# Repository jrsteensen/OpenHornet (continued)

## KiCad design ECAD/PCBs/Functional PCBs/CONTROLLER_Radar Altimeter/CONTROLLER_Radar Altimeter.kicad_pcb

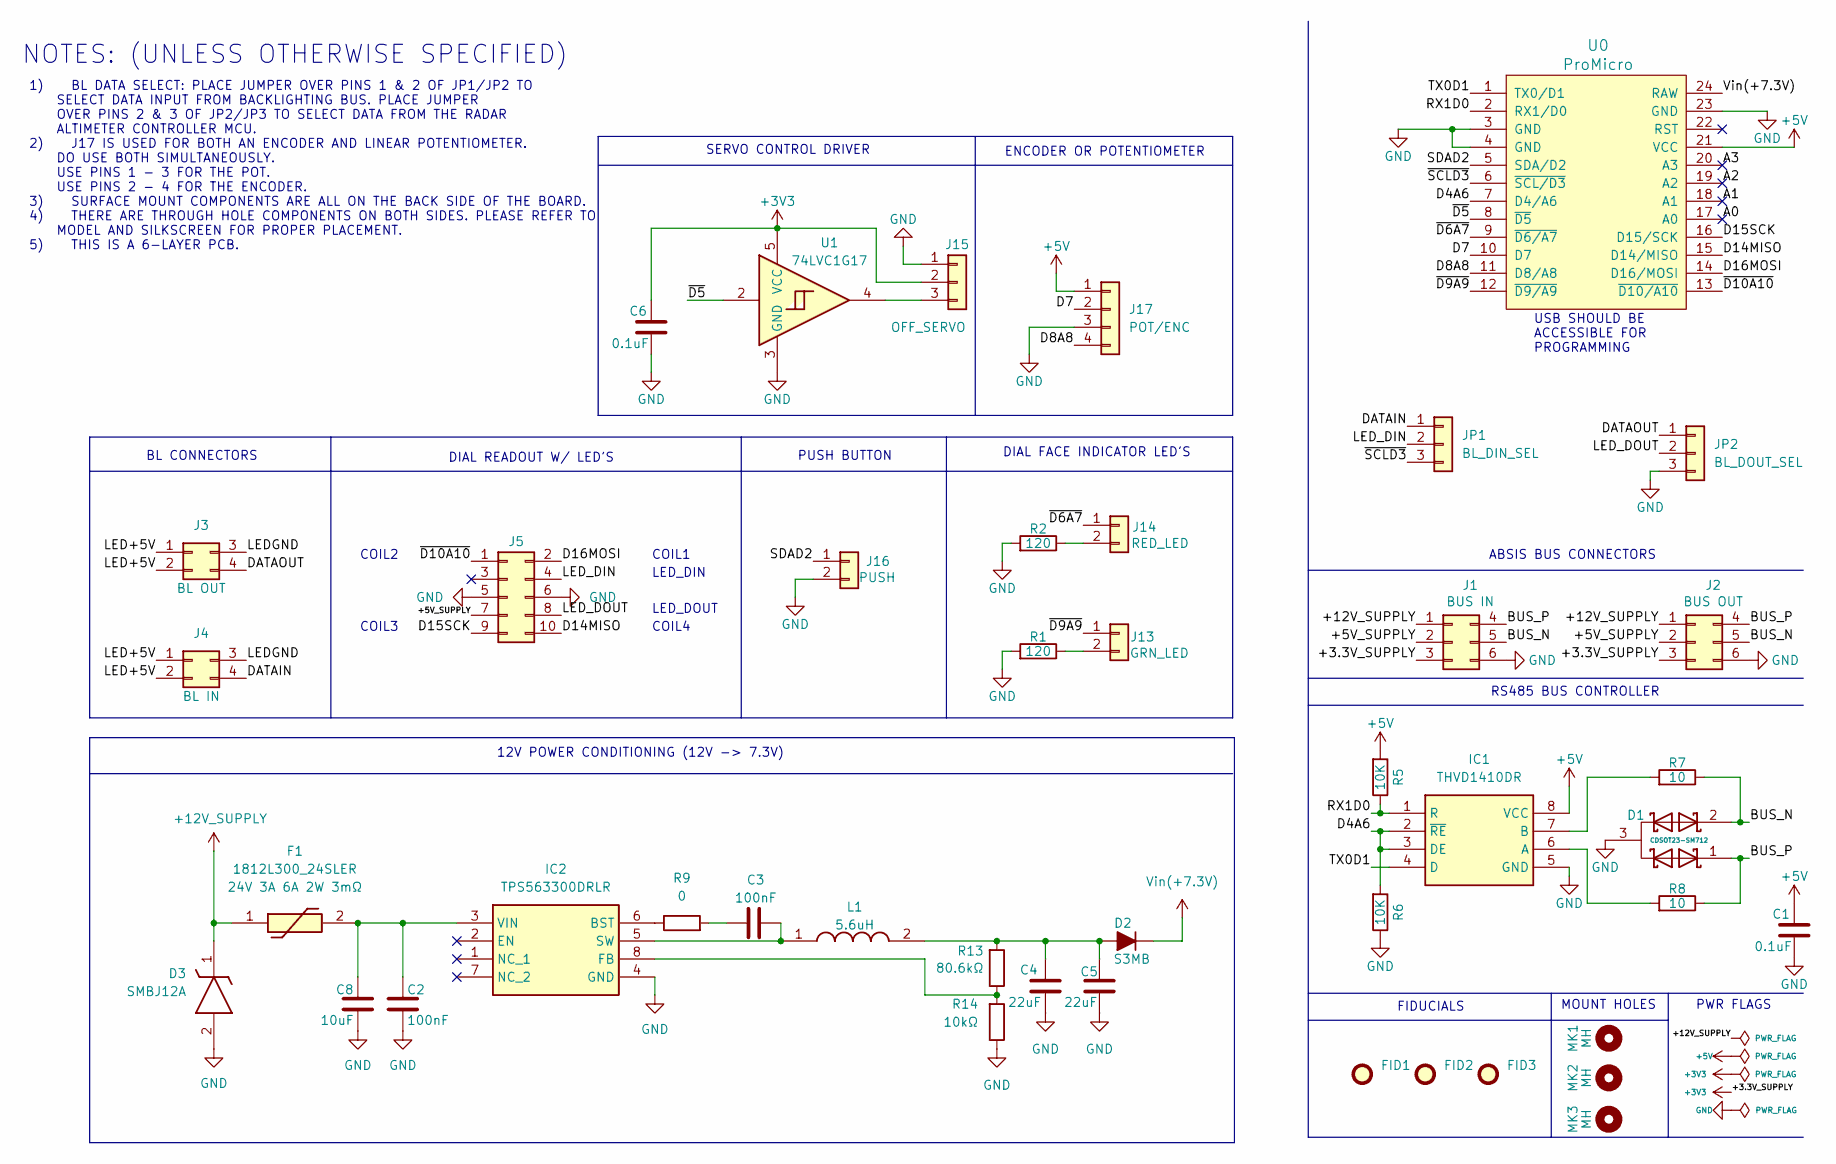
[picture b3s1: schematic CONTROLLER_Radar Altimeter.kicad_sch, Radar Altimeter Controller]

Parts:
C1, C6: 0.1uF; C_0603_1608Metric; Manufacturer PN CC0603KRX7R9BB104; LCSC C14663
C2, C3: 100nF; C_0402_1005Metric; Manufacturer PN CL05B104KB54PNC; LCSC C307331
C4, C5: 22uF; C_0805_2012Metric; Manufacturer PN CL21A226MAQNNNE; LCSC C45783
C8: 10uF; C_0603_1608Metric; Manufacturer PN CL10A106MA8NRNC; LCSC C96446
D1: CDSOT23-SM712; Manufacturer_Part_Number CDSOT23-SM712; Mouser Part Number 652-CDSOT23-SM712
D2: S3MB; D_SMB; Manufacturer PN S3MB; LCSC C47524
D3: SMBJ12A; D_SMB; Manufacturer PN SMBJ12A; LCSC C151251
F1: 1812L300_24SLER; Fuse_1812_4532Metric; Manufacturer PN 1812L300/24SLER; LCSC C1512049
FID1, FID2, FID3: Fiducial; Fiducial_1mm_Mask2mm
IC1: THVD1410DR; Manufacturer_Part_Number THVD1410DR; Mouser Part Number 595-THVD1410DR
IC2: TPS563300DRLR; SOT-583-8; Manufacturer PN TPS563300DRLR; LCSC C5219249
J1: BUS IN; Molex_Mini-Fit_Jr_5566-06A_2x03_P4.20mm_Vertical; Manufacturer PN 39-28-1063; LCSC C471417
J2: BUS OUT; Molex_Mini-Fit_Jr_5566-06A_2x03_P4.20mm_Vertical; Manufacturer PN 39-28-1063; LCSC C471417
J3: BL OUT; Molex_Mini-Fit_Jr_5566-04A_2x02_P4.20mm_Vertical; Manufacturer PN 39-28-1043; LCSC C293502
J4: BL IN; Molex_Mini-Fit_Jr_5566-04A_2x02_P4.20mm_Vertical; Manufacturer PN 39-28-1043; LCSC C293502
J5: Conn_02x05_Odd_Even; PinHeader_2x05_P2.54mm_Vertical
J13: GRN_LED; PinHeader_1x02_P2.54mm_Vertical; Manufacturer PN PH1-02-UA
J14: RED_LED; PinHeader_1x02_P2.54mm_Vertical; Manufacturer PN PH1-02-UA
J15: OFF_SERVO; Adam-Tech_1x03_P1.25mm_Vertical; Manufacturer PN PH1-03-UA
J16: PUSH; PinHeader_1x02_P2.54mm_Vertical; Manufacturer PN PH1-02-UA
J17: POT/ENC; PinHeader_1x04_P2.54mm_Vertical
JP1: BL_DIN_SEL; PinHeader_1x03_P2.54mm_Vertical
JP2: BL_DOUT_SEL; PinHeader_1x03_P2.54mm_Vertical
L1: 5.6uH; L_Bourns_SRP6060FA; Manufacturer PN SRP6060FA-5R6M; LCSC C1332221
MK1, MK2, MK3: MH; MountingHole_2.5mm
R1, R2: 120; R_0805_2012Metric_Pad1.15x1.40mm_HandSolder; Manufacturer PN 0805W8F1200T5E; LCSC C17437
R5, R6: 10K; R_0603_1608Metric_Pad0.98x0.95mm_HandSolder; LCSC C25804
R7, R8: 10; R_0603_1608Metric_Pad0.98x0.95mm_HandSolder; LCSC C844519
R9: 0; R_0402_1005Metric; Manufacture PN 0402WGF0000TCE; LCSC C17168
R13: 80.6kΩ; R_0402_1005Metric; Manufacturer PN 0402WGF8062TCE; LCSC C25921
R14: 10kΩ; R_0402_1005Metric; Manufacturer PN 0402WGF1002TCE; LCSC C25744
U0: ProMicro; DIP-24_W15.24mm_Socket; LCSC C72120
U1: 74LVC1G17; SOT-23-5; LCSC C7836

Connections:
+3V3: C6.2, J1.3, J2.3, J15.2, U1.5 (VCC)
+5V: C1.2, IC1.8 (VCC), J17.1, R5.2, U0.21 (VCC)
+12V_SUPPLY: D3.1 (K), F1.1, J1.1, J2.1
/+5V_SUPPLY: J1.2, J2.2, J5.7
/A0: U0.17 (A0)
/A1: U0.18 (A1)
/A2: U0.19 (A2)
/A3: U0.20 (A3)
/BUS_N: D1.2, J1.5, J2.5, R7.2
/BUS_P: D1.1, J1.4, J2.4, R8.2
/D4A6: IC1.2 (~RE), IC1.3 (DE), R6.2, U0.7 (D4/A6)
/D7: J17.2, U0.10 (D7)
/D8A8: J17.4, U0.11 (D8/A8)
/D14MISO: J5.10, U0.15 (D14/MISO)
/D15SCK: J5.9, U0.16 (D15/SCK)
/D16MOSI: J5.2, U0.14 (D16/MOSI)
/DATAIN: J4.4, JP1.1
/DATAOUT: J3.4, JP2.1
/LED+5V: J3.1, J3.2 (Pin_3), J4.1, J4.2 (Pin_3)
/LEDGND: J3.3 (Pin_2), J4.3 (Pin_2)
/LED_DIN: J5.4, JP1.2
/LED_DOUT: J5.8, JP2.2
/RX1D0: IC1.1 (R), R5.1, U0.2 (RX1/D0)
/SDAD2: J16.1, U0.5 (SDA/D2)
/TX0D1: IC1.4 (D), U0.1 (TX0/D1)
/~D5: U0.8 (~D5), U1.2
/~D6A7: J14.1, U0.9 (~D6/A7)
/~D9A9: J13.1, U0.12 (~D9/A9)
/~D10A10: J5.1, U0.13 (~D10/A10)
/~SCLD3: JP1.3, U0.6 (~SCL/D3)
GND: C1.1, C2.1, C4.2, C5.2, C6.1, C8.1, D1.3, D3.2 (A), IC1.5 (GND), IC2.4 (GND), J1.6, J2.6, J5.5, J5.6, J15.1, J16.2, J17.3, JP2.3, R1.1, R2.1, R6.1, R14.1, U0.3 (GND), U0.4 (GND), U0.23 (GND), U1.3 (GND)
unnamed: C3.2, R9.2
unnamed: C4.1, C5.1, D2.2 (A), L1.2, R13.2
unnamed: IC1.6 (A), R8.1
unnamed: IC1.7 (B), R7.1
unnamed: IC2.6 (BST), R9.1
unnamed: IC2.8 (FB), R13.1, R14.2
unnamed: C3.1, IC2.5 (SW), L1.1
unnamed: C2.2, C8.2, F1.2, IC2.3 (VIN)
unnamed: J13.2, R1.2
unnamed: J14.2, R2.2
unnamed: J15.3, U1.4
Vin(+7.3V): D2.1 (K), U0.24 (RAW)

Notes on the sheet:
ABSIS BUS CONNECTORS
RS485 BUS CONTROLLER
12V POWER CONDITIONING (12V -> 7.3V)
USB SHOULD BE ACCESSIBLE FOR PROGRAMMING
MOUNT HOLES
COIL3
FIDUCIALS
DIAL READOUT W/ LED'S
COIL4
ENCODER OR POTENTIOMETER
NOTES: (UNLESS OTHERWISE SPECIFIED)
PUSH BUTTON
LED_DOUT
1) BL DATA SELECT: PLACE JUMPER OVER PINS 1 & 2 OF JP1/JP2 TO SELECT DATA INPUT FROM BACKLIGHTING BUS. PLACE JUMPER OVER PINS 2 & 3 OF JP2/JP3 TO SELECT DATA FROM THE RADAR ALTIMETER CONTROLLER MCU. 2) J17 IS USED FOR BOTH AN ENCODER AND LINEAR POTENTIOMETER. DO USE BOTH SIMULTANEOUSLY. USE PINS 1 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
COIL2
COIL1
DIAL FACE INDICATOR LED'S
PWR FLAGS
LED_DIN
SERVO CONTROL DRIVER
BL CONNECTORS

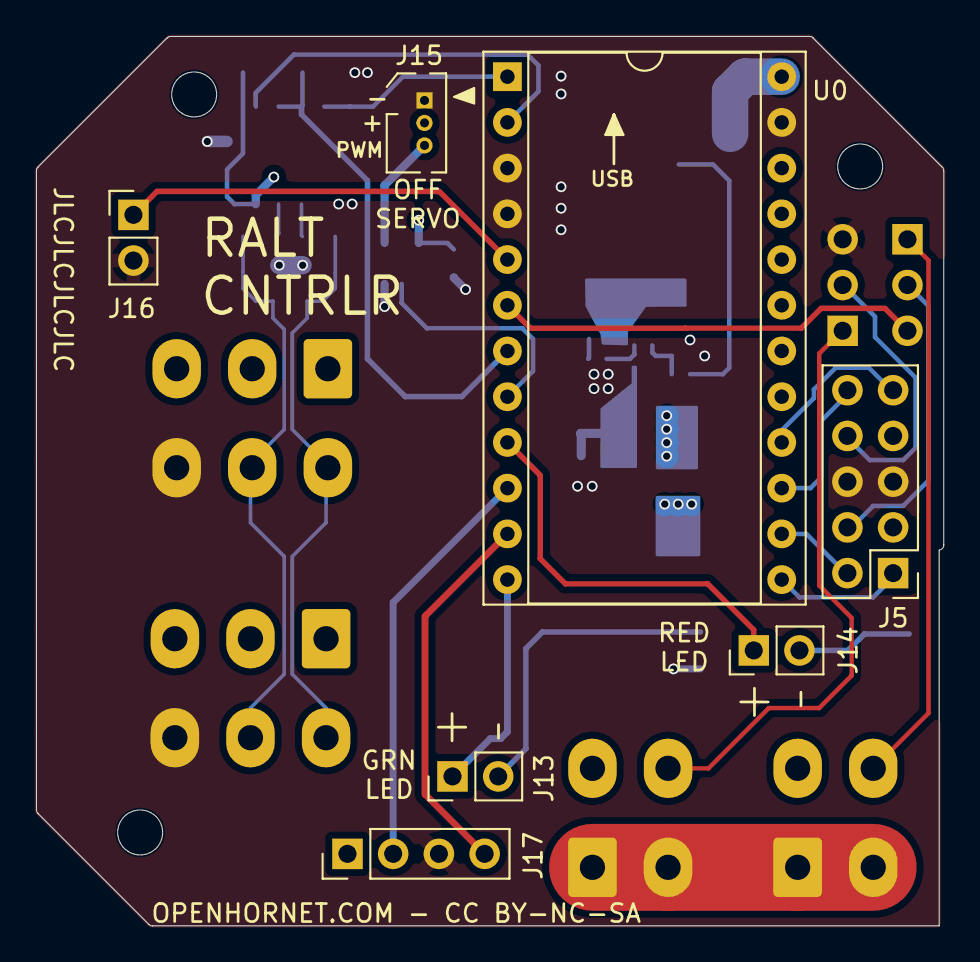
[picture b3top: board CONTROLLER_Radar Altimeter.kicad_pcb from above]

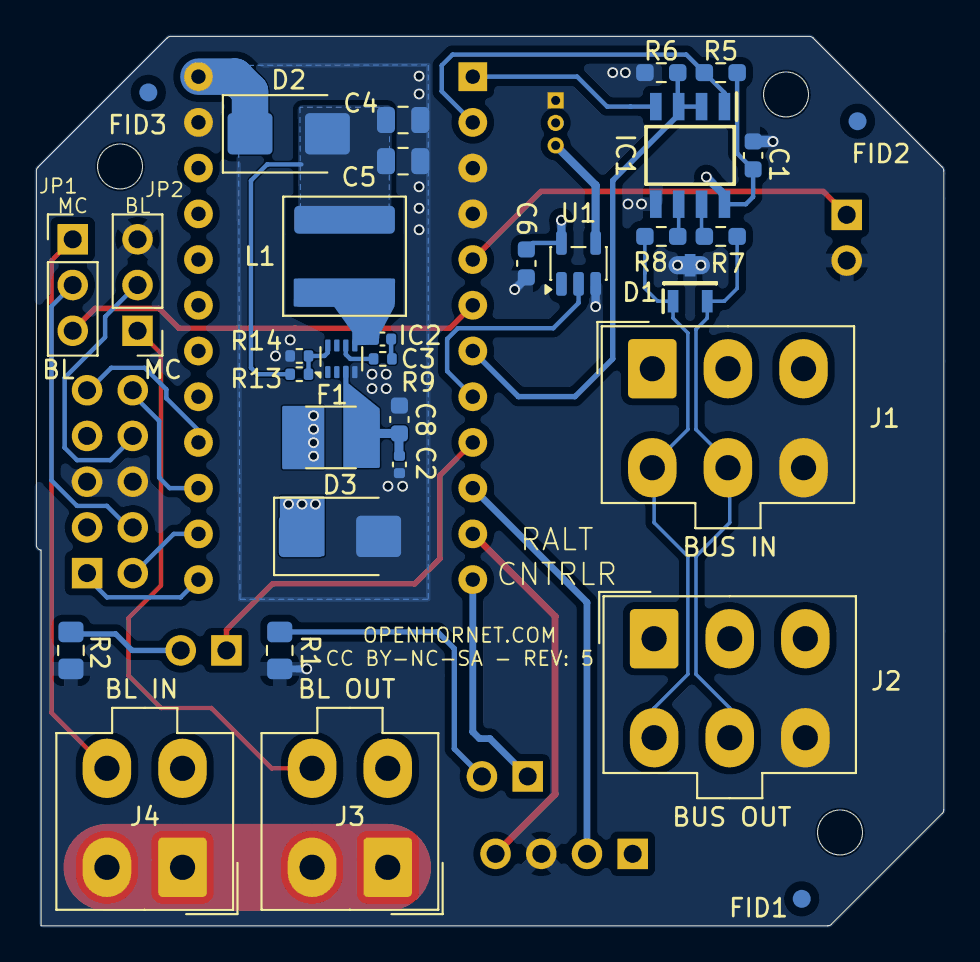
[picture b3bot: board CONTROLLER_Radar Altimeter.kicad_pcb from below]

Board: 6 copper layers, 50.4 x 49.4 mm, 43 parts (33 on the bottom side), 39 nets.

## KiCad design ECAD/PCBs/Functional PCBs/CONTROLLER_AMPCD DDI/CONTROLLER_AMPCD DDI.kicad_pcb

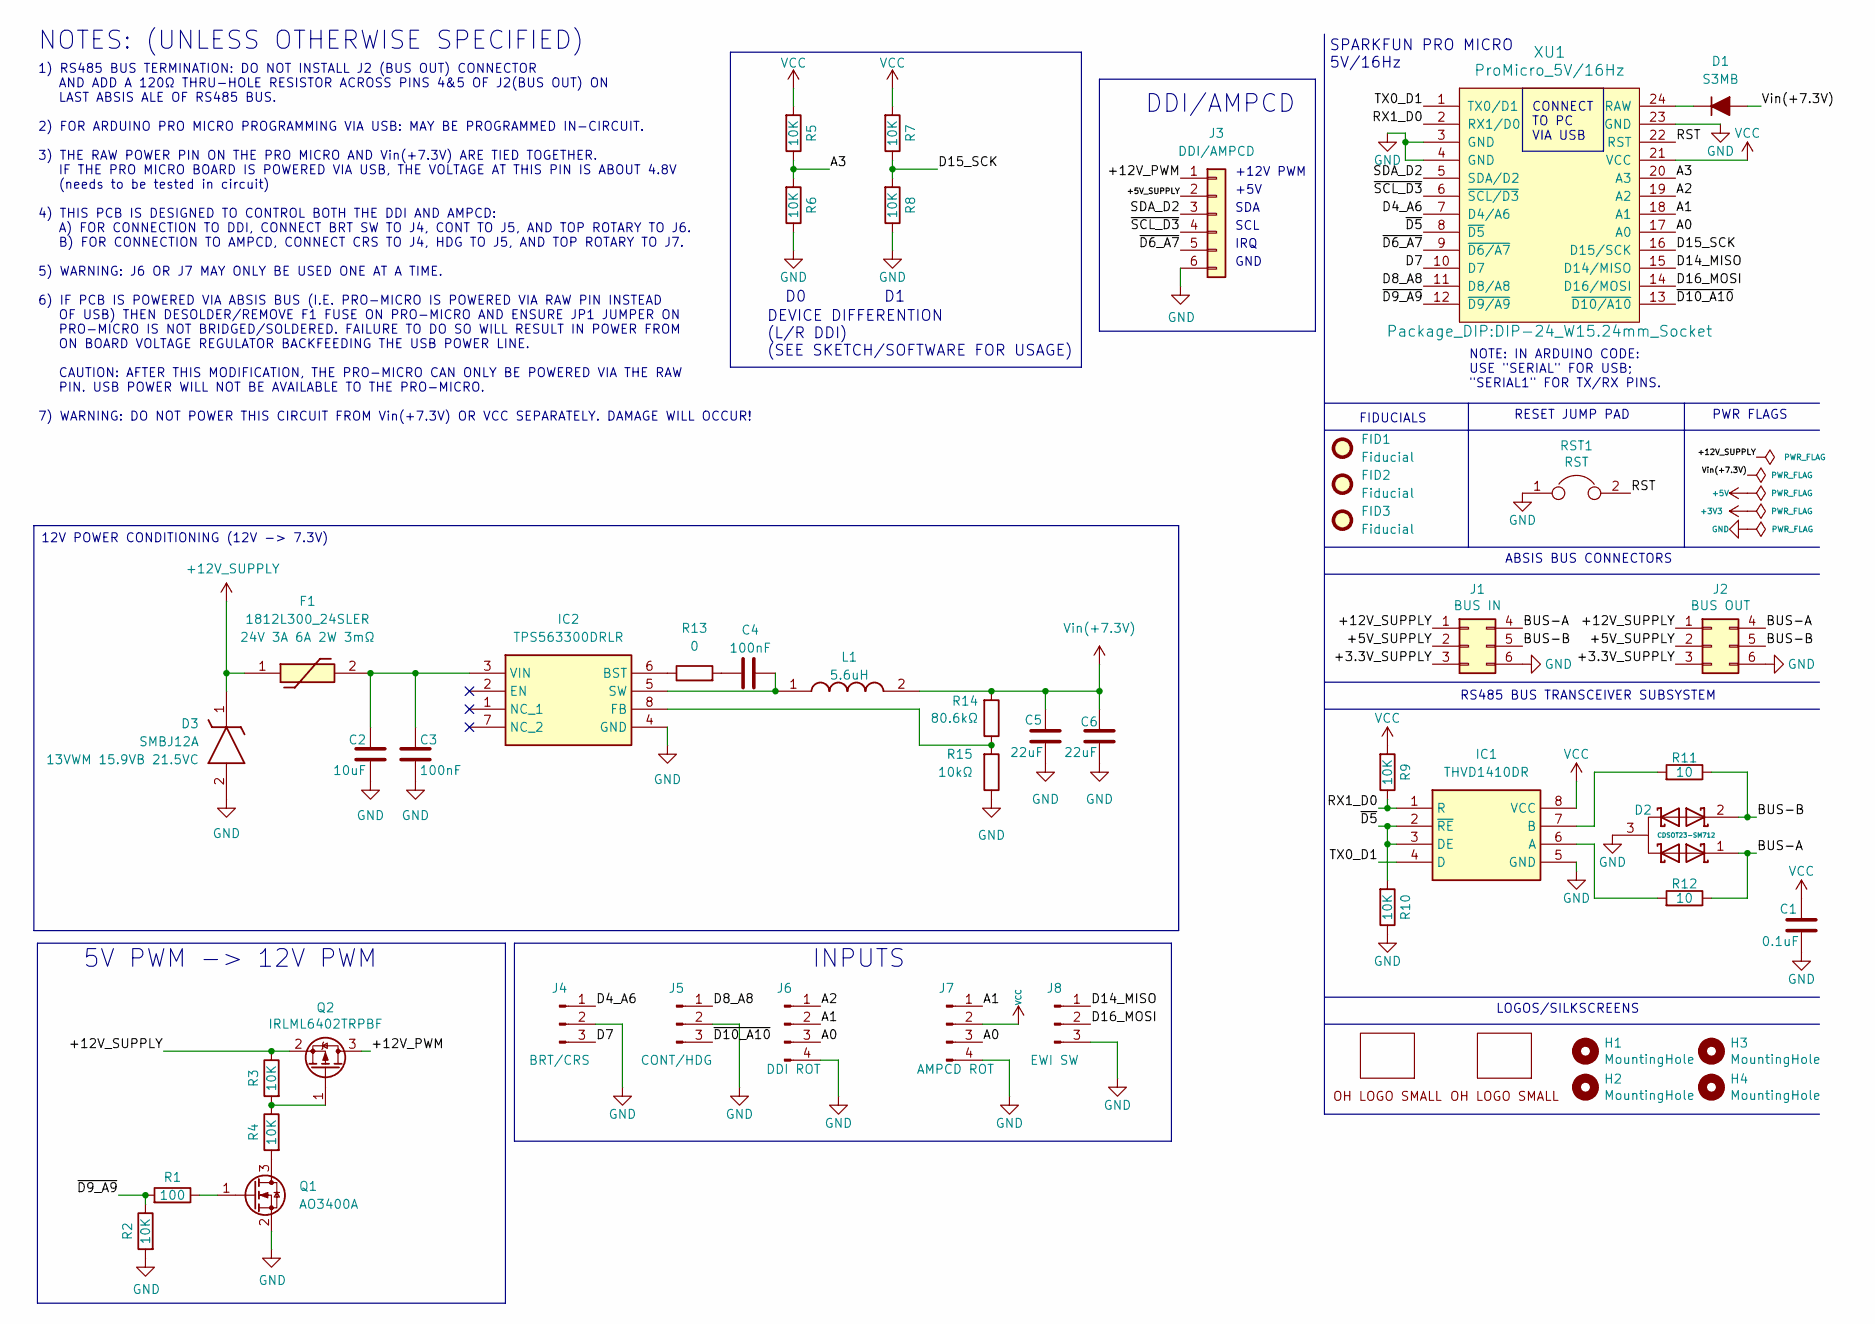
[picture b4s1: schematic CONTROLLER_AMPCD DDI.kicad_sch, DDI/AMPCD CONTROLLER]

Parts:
C1: 0.1uF; C_0603_1608Metric; Manufacturer PN CC0603KRX7R9BB104; LCSC C14663
C2: 10uF; C_0603_1608Metric; Manufacturer PN CL10A106MA8NRNC; LCSC C96446
C3, C4: 100nF; C_0402_1005Metric; Manufacturer PN CL05B104KB54PNC; LCSC C307331
C5, C6: 22uF; C_0805_2012Metric; Manufacturer PN CL21A226MAQNNNE; LCSC C45783
D1: S3MB; D_SMB; Manufacturer PN S3MB; LCSC C47524
D2: CDSOT23-SM712; Manufacturer_Part_Number CDSOT23-SM712; Mouser Part Number 652-CDSOT23-SM712
D3: SMBJ12A; D_SMB; Manufacturer PN SMBJ12A; LCSC C151251
F1: 1812L300_24SLER; Fuse_1812_4532Metric; Manufacturer PN 1812L300/24SLER; LCSC C1512049
FID1, FID2, FID3: Fiducial; Fiducial_1mm_Mask2mm
H1, H2, H3, H4: MountingHole; MountingHole_3.2mm_M3
IC1: THVD1410DR; Manufacturer_Part_Number THVD1410DR; Mouser Part Number 595-THVD1410DR
IC2: TPS563300DRLR; SOT-583-8; Manufacturer PN TPS563300DRLR; LCSC C5219249
J1: BUS IN; Molex_Mini-Fit_Jr_5566-06A2_2x03_P4.20mm_Vertical; LCSC N/A
J2: BUS OUT; Molex_Mini-Fit_Jr_5566-06A2_2x03_P4.20mm_Vertical; LCSC N/A
J3: DDI/AMPCD; Molex_KK-254_AE-6410-06A_1x06_P2.54mm_Vertical
J4: BRT/CRS; Molex_KK-254_AE-6410-03A_1x03_P2.54mm_Vertical
J5: CONT/HDG; Molex_KK-254_AE-6410-03A_1x03_P2.54mm_Vertical
J6: DDI ROT; Molex_KK-254_AE-6410-04A_1x04_P2.54mm_Vertical
J7: AMPCD ROT; Molex_KK-254_AE-6410-04A_1x04_P2.54mm_Vertical
J8: EWI SW; Molex_KK-254_AE-6410-03A_1x03_P2.54mm_Vertical
L1: 5.6uH; L_Bourns_SRP6060FA; Manufacturer PN SRP6060FA-5R6M; LCSC C1332221
LOGO1: OpenHornetLogoSmall; LOGO_OH_NoText_Small; LCSC N/A
LOGO2: OpenHornetLogoSmall; LOGO_OH_Text_Small; LCSC N/A
Q1: AO3400A; SOT-23; Manufacture PN AO3400A; LCSC C20917
Q2: IRLML6402TRPBF; SOT-23; LCSC C2593
R1: 100; R_0603_1608Metric_Pad0.98x0.95mm_HandSolder; LCSC C22775
R2, R3, R4, R5, R6, R7, R8, R9, R10: 10K; R_0603_1608Metric_Pad0.98x0.95mm_HandSolder; LCSC C25804
R11, R12: 10; R_0603_1608Metric_Pad0.98x0.95mm_HandSolder; LCSC C844519
R13: 0; R_0402_1005Metric; Manufacture PN 0402WGF0000TCE; LCSC C17168
R14: 80.6kΩ; R_0402_1005Metric; Manufacturer PN 0402WGF8062TCE; LCSC C25921
R15: 10kΩ; R_0402_1005Metric; Manufacturer PN 0402WGF1002TCE; LCSC C25744
RST1: RST; SolderJumper-2_P1.3mm_Open_RoundedPad1.0x1.5mm
XU1: ProMicro_5V/16Hz; DIP-24_W15.24mm_Socket; LCSC C72120

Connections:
+12V_SUPPLY: D3.1 (K), F1.1, J1.1, J2.1, Q2.2 (S), R3.1
/+3.3V_SUPPLY: J1.3, J2.3
/+5V_SUPPLY: J1.2, J2.2, J3.2
/+12V_PWM: J3.1, Q2.3 (D)
/A0: J6.3, J7.3, XU1.17 (A0)
/A1: J6.2, J7.1, XU1.18 (A1)
/A2: J6.1, XU1.19 (A2)
/A3: R5.1, R6.2, XU1.20 (A3)
/BUS-A: D2.1, J1.4, J2.4, R12.2
/BUS-B: D2.2, J1.5, J2.5, R11.2
/D4_A6: J4.1, XU1.7 (D4/A6)
/D7: J4.3, XU1.10 (D7)
/D8_A8: J5.1, XU1.11 (D8/A8)
/D14_MISO: J8.1, XU1.15 (D14/MISO)
/D15_SCK: R7.1, R8.2, XU1.16 (D15/SCK)
/D16_MOSI: J8.2, XU1.14 (D16/MOSI)
/RST: RST1.2, XU1.22 (RST)
/RX1_D0: IC1.1 (R), R9.1, XU1.2 (RX1/D0)
/SDA_D2: J3.3, XU1.5 (SDA/D2)
/TX0_D1: IC1.4 (D), XU1.1 (TX0/D1)
/~D5: IC1.2 (~RE), IC1.3 (DE), R10.2, XU1.8 (~D5)
/~D6_A7: J3.5, XU1.9 (~D6/A7)
/~D9_A9: R1.2, R2.1, XU1.12 (~D9/A9)
/~D10_A10: J5.3, XU1.13 (~D10/A10)
/~SCL_D3: J3.4, XU1.6 (~SCL/D3)
GND: C1.1, C2.1, C3.1, C5.2, C6.2, D2.3, D3.2 (A), IC1.5 (GND), IC2.4 (GND), J1.6, J2.6, J3.6, J4.2, J5.2, J6.4, J7.4, J8.3, Q1.2 (S), R2.2, R6.1, R8.1, R10.1, R15.1, RST1.1, XU1.3 (GND), XU1.4 (GND), XU1.23 (GND)
unnamed: C4.2, R13.2
unnamed: D1.1 (K), XU1.24 (RAW)
unnamed: IC1.6 (A), R12.1
unnamed: IC1.7 (B), R11.1
unnamed: IC2.6 (BST), R13.1
unnamed: IC2.8 (FB), R14.1, R15.2
unnamed: C4.1, IC2.5 (SW), L1.1
unnamed: C2.2, C3.2, F1.2, IC2.3 (VIN)
unnamed: Q1.3 (D), R4.2
unnamed: Q1.1 (G), R1.1
unnamed: Q2.1 (G), R3.2, R4.1
VCC: C1.2, IC1.8 (VCC), J7.2, R5.2, R7.2, R9.2, XU1.21 (VCC)
Vin(+7.3V): C5.1, C6.1, D1.2 (A), L1.2, R14.2

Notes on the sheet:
IRQ
FIDUCIALS
RS485 BUS TRANSCEIVER SUBSYSTEM
NOTES: (UNLESS OTHERWISE SPECIFIED)
DEVICE DIFFERENTION (L/R DDI) (SEE SKETCH/SOFTWARE FOR USAGE)
SPARKFUN PRO MICRO 5V/16Hz
CONNECT TO PC VIA USB
RESET JUMP PAD
LOGOS/SILKSCREENS
+12V PWM
5V PWM -> 12V PWM
SCL
PWR FLAGS
+5V
ABSIS BUS CONNECTORS
NOTE: IN ARDUINO CODE: USE "SERIAL" FOR USB; "SERIAL1" FOR TX/RX PINS.
SDA
INPUTS
1) RS485 BUS TERMINATION: DO NOT INSTALL J2 (BUS OUT) CONNECTOR AND ADD A 120Ω THRU-HOLE RESISTOR ACROSS PINS 4&5 OF J2(BUS OUT) ON LAST ABSIS ALE OF RS485 BUS. 2) FOR ARDUINO PRO MICRO PROGRAMMING VIA USB: MAY BE PROGRAMMED IN-CIRCUIT. 3) THE RAW POWER PIN ON THE PRO MICRO AND Vin(+7.3V) ARE TIED 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
GND
DDI/AMPCD
12V POWER CONDITIONING (12V -> 7.3V)

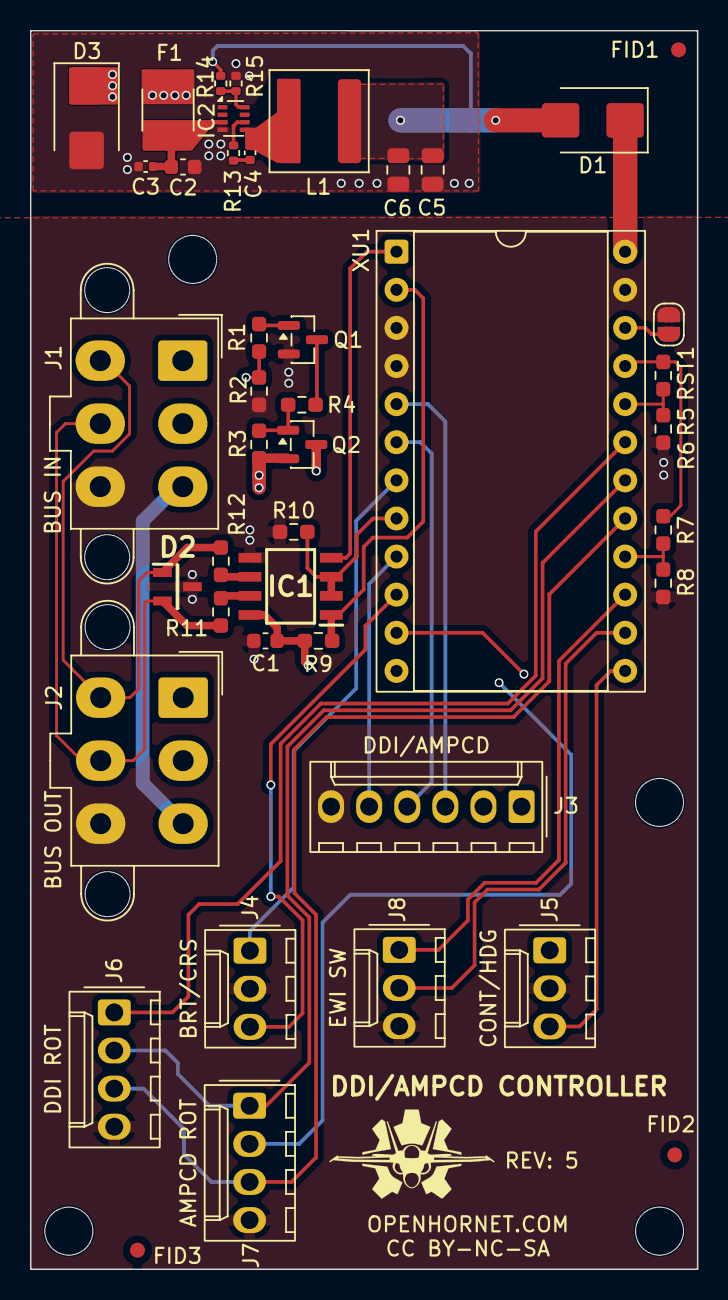
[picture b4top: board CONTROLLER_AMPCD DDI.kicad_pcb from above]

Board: 4 copper layers, 44.5 x 82.5 mm, 49 parts (1 on the bottom side), 39 nets.

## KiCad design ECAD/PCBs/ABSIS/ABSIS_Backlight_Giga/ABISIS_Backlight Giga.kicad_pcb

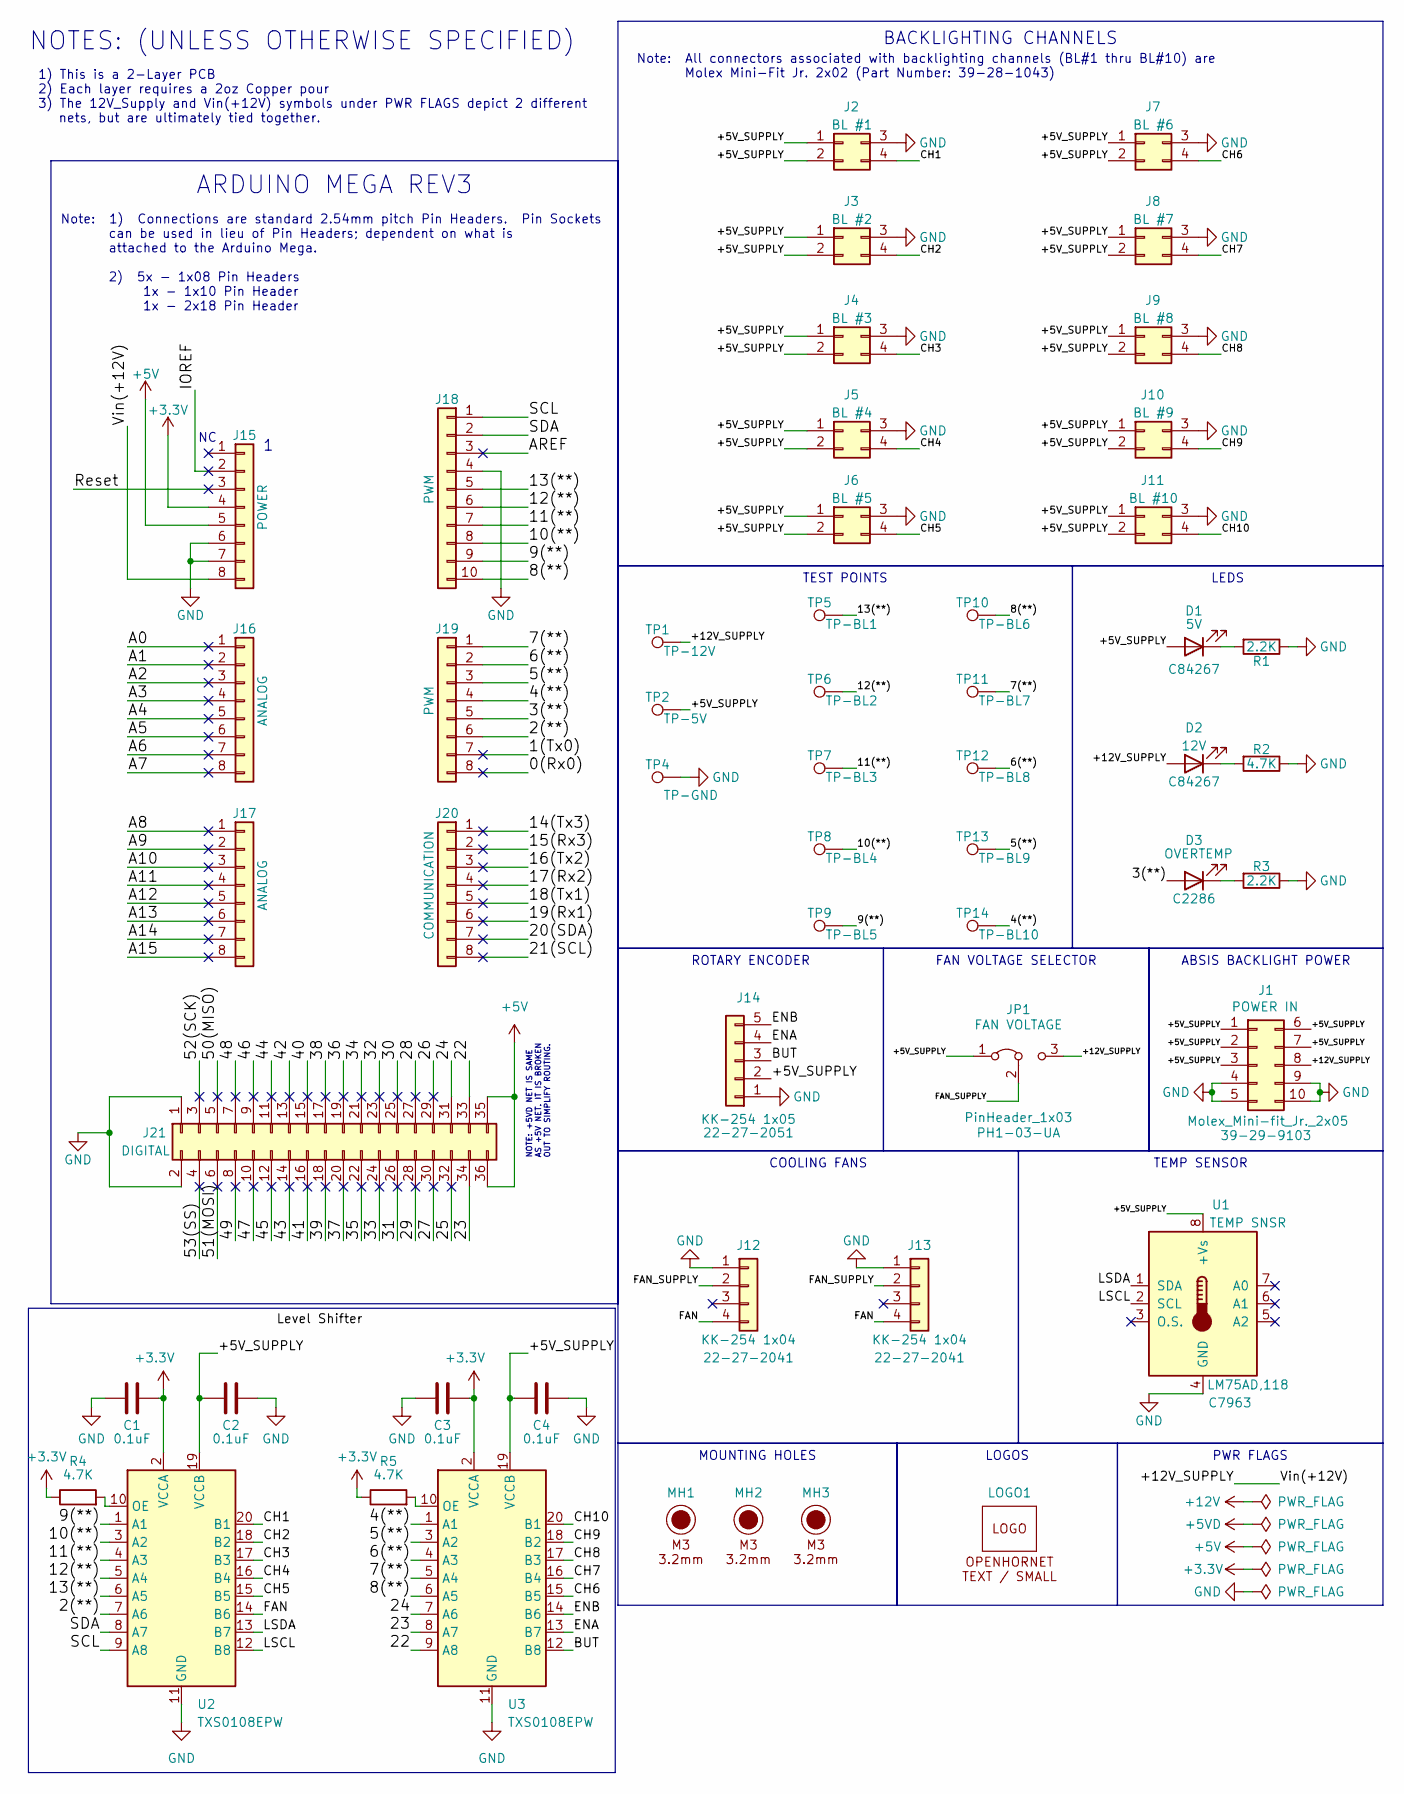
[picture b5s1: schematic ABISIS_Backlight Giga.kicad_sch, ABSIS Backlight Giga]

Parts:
C1, C2, C3, C4: 0.1uF; C_0603_1608Metric; Manufacturer PN CC0603KRX7R9BB104; LCSC C14663
D1, D2: Green; LED_0603_1608Metric_Pad1.05x0.95mm_HandSolder; Manufacturer PN NCD0603G1; LCSC C84267
D3: Red; LED_0603_1608Metric_Pad1.05x0.95mm_HandSolder; Manufacturer PN KT-0603R; LCSC C2286
J1: Molex_Mini-fit_Jr._2x05; Molex_Mini-Fit_Jr_5566-10A2_2x05_P4.20mm_Vertical; Manufacturer PN 39-29-9103; LCSC C587474
J2, J3, J4, J5, J6, J7, J8, J9, J10, J11: Mini-Fit Jr. 2x02; Molex_Mini-Fit_Jr_5566-04A_2x02_P4.20mm_Vertical; Manufacturer PN 39-28-1043; LCSC C293502
J12, J13: KK-254 1x04; Molex_KK-254_AE-6410-04A_1x04_P2.54mm_Vertical; Manufacturer PN 22-27-2041; LCSC C504991
J14: KK-254 1x05; Molex_KK-254_AE-6410-05A_1x05_P2.54mm_Vertical; Manufacturer PN 22-27-2051; LCSC C585785
J15, J16, J17, J19, J20: PinHeader_1x08; PinHeader_1x08_P2.54mm_Vertical; Manufacturer PN PH1-08-UA
J18: PinHeader_1x10; PinHeader_1x10_P2.54mm_Vertical; Manufacturer PN PH1-10-UA
J21: PinHeader_2x18; PinHeader_2x18_P2.54mm_Vertical; Manufacturer PN PH2-18-UA
JP1: PinHeader_1x03; PinHeader_1x03_P2.54mm_Vertical; Manufacturer PN PH1-03-UA
LOGO1: LOGO; LOGO_OH_Text_Small
MH1, MH2, MH3: M3 / 3.2mm; MountingHole_3.2mm_M3_DIN965
R1, R3: 2.2K; R_0603_1608Metric; Manufacturer PN 0603WAF2201T5E; LCSC C4190
R2, R4, R5: 4.7K; R_0603_1608Metric; Manufacturer PN 0603WAF4701T5E; LCSC C23162
TP1, TP2, TP4, TP5, TP6, TP7, TP8, TP9, TP10, TP11, TP12, TP13, TP14: TestPoint; TestPoint_THTPad_D1.5mm_Drill0.7mm
U1: LM75AD,118; SOIC-8_3.9x4.9mm_P1.27mm; Manufacturer PN LM75AD,118; LCSC C7963
U2, U3: TXS0108EPW; TSSOP-20_4.4x6.5mm_P0.65mm

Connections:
+3.3V: C1.2, C3.2, J15.4, R4.1, R5.1, U2.2 (VCCA), U3.2 (VCCA)
+5V: J15.5, J21.35, J21.36
/0(Rx0): J19.8
/1(Tx0): J19.7
/2(**): J19.6, U2.7 (A6)
/3(**): D3.2 (A), J19.5
/4(**): J19.4, TP14.1 (1_1), U3.1 (A1)
/5(**): J19.3, TP13.1 (1_1), U3.3 (A2)
/6(**): J19.2, TP12.1 (1_1), U3.4 (A3)
/7(**): J19.1, TP11.1 (1_1), U3.5 (A4)
/8(**): J18.10, TP10.1 (1_1), U3.6 (A5)
/9(**): J18.9, TP9.1 (1_1), U2.1 (A1)
/10(**): J18.8, TP8.1 (1_1), U2.3 (A2)
/11(**): J18.7, TP7.1 (1_1), U2.4 (A3)
/12(**): J18.6, TP6.1 (1_1), U2.5 (A4)
/13(**): J18.5, TP5.1 (1_1), U2.6 (A5)
/14(Tx3): J20.1
/15(Rx3): J20.2
/16(Tx2): J20.3
/17(Rx2): J20.4
/18(Tx1): J20.5
/19(Rx1): J20.6
/20(SDA): J20.7
/21(SCL): J20.8
/22: J21.33, U3.9 (A8)
/23: J21.34, U3.8 (A7)
/24: J21.31, U3.7 (A6)
/25: J21.32
/26: J21.29
/27: J21.30
/28: J21.27
/29: J21.28
/30: J21.25
/31: J21.26
/32: J21.23
/33: J21.24
/34: J21.21
/35: J21.22
/36: J21.19
/37: J21.20
/38: J21.17
/39: J21.18
/40: J21.15
/41: J21.16
/42: J21.13
/43: J21.14
/44: J21.11
/45: J21.12
/46: J21.9
/47: J21.10
/48: J21.7
/49: J21.8
/50(MISO): J21.5
/51(MOSI): J21.6
/52(SCK): J21.3
/53(SS): J21.4
/+5V_SUPPLY: C2.1, C4.1, D1.2 (A), J1.1, J1.2, J1.3, J1.6, J1.7, J2.1, J2.2 (Pin_3), J3.1, J3.2 (Pin_3), J4.1, J4.2 (Pin_3), J5.1, J5.2 (Pin_3), J6.1, J6.2 (Pin_3), J7.1, J7.2 (Pin_3), J8.1, J8.2 (Pin_3), J9.1, J9.2 (Pin_3), J10.1, J10.2 (Pin_3), J11.1, J11.2 (Pin_3), J14.2, JP1.1 (A), TP2.1 (1_1), U1.8 (+Vs), U2.19 (VCCB), U3.19 (VCCB)
/+12V_SUPPLY: D2.2 (A), J1.8, J15.8, JP1.3 (B), TP1.1 (1_1)
/A0: J16.1
/A1: J16.2
/A2: J16.3
/A3: J16.4
/A4: J16.5
/A5: J16.6
/A6: J16.7
/A7: J16.8
/A8: J17.1
/A9: J17.2
/A10: J17.3
/A11: J17.4
/A12: J17.5
/A13: J17.6
/A14: J17.7
/A15: J17.8
/AREF: J18.3
/BUT: J14.3, U3.12 (B8)
/CH1: J2.4, U2.20 (B1)
/CH2: J3.4, U2.18 (B2)
/CH3: J4.4, U2.17 (B3)
/CH4: J5.4, U2.16 (B4)
/CH5: J6.4, U2.15 (B5)
/CH6: J7.4, U3.15 (B5)
/CH7: J8.4, U3.16 (B4)
/CH8: J9.4, U3.17 (B3)
/CH9: J10.4, U3.18 (B2)
/CH10: J11.4, U3.20 (B1)
/ENA: J14.4, U3.13 (B7)
/ENB: J14.5, U3.14 (B6)
/FAN: J12.4, J13.4, U2.14 (B6)
/FAN_SUPPLY: J12.2, J13.2, JP1.2 (C)
/IOREF: J15.2
/LSCL: U1.2 (SCL), U2.12 (B8)
/LSDA: U1.1 (SDA), U2.13 (B7)
/Reset: J15.3
/SCL: J18.1, U2.9 (A8)
/SDA: J18.2, U2.8 (A7)
GND: C1.1, C2.2, C3.1, C4.2, J1.4, J1.5, J1.9, J1.10, J2.3 (Pin_2), J3.3 (Pin_2), J4.3 (Pin_2), J5.3 (Pin_2), J6.3 (Pin_2), J7.3 (Pin_2), J8.3 (Pin_2), J9.3 (Pin_2), J10.3 (Pin_2), J11.3 (Pin_2), J12.1, J13.1, J14.1, J15.6, J15.7, J18.4, J21.1, J21.2, R1.1, R2.1, R3.1, TP4.1 (1_1), U1.4 (GND), U2.11 (GND), U3.11 (GND)
unnamed: D1.1 (K), R1.2
unnamed: D2.1 (K), R2.2
unnamed: D3.1 (K), R3.2
unnamed: R4.2, U2.10 (OE)
unnamed: R5.2, U3.10 (OE)

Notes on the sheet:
1) This is a 2-Layer PCB 2) Each layer requires a 2oz Copper pour 3) The 12V_Supply and Vin(+12V) symbols under PWR FLAGS depict 2 different nets, but are ultimately tied together.
Note: All connectors associated with backlighting channels (BL#1 thru BL#10) are Molex Mini-Fit Jr. 2x02 (Part Number: 39-28-1043)
NOTE: +5VD NET IS SAME AS +5V NET. IT IS BROKEN OUT TO SIMPLIFY ROUTING.
Note: 1) Connections are standard 2.54mm pitch Pin Headers. Pin Sockets can be used in lieu of Pin Headers; dependent on what is attached to the Arduino Mega. 2) 5x - 1x08 Pin Headers 1x - 1x10 Pin Header 1x - 2x18 Pin Header
NOTES: (UNLESS OTHERWISE SPECIFIED)
LEDS
BACKLIGHTING CHANNELS
ABSIS BACKLIGHT POWER
ROTARY ENCODER
ARDUINO MEGA REV3
TEMP SENSOR
PWR FLAGS
COOLING FANS
LOGOS
FAN VOLTAGE SELECTOR
MOUNTING HOLES
TEST POINTS

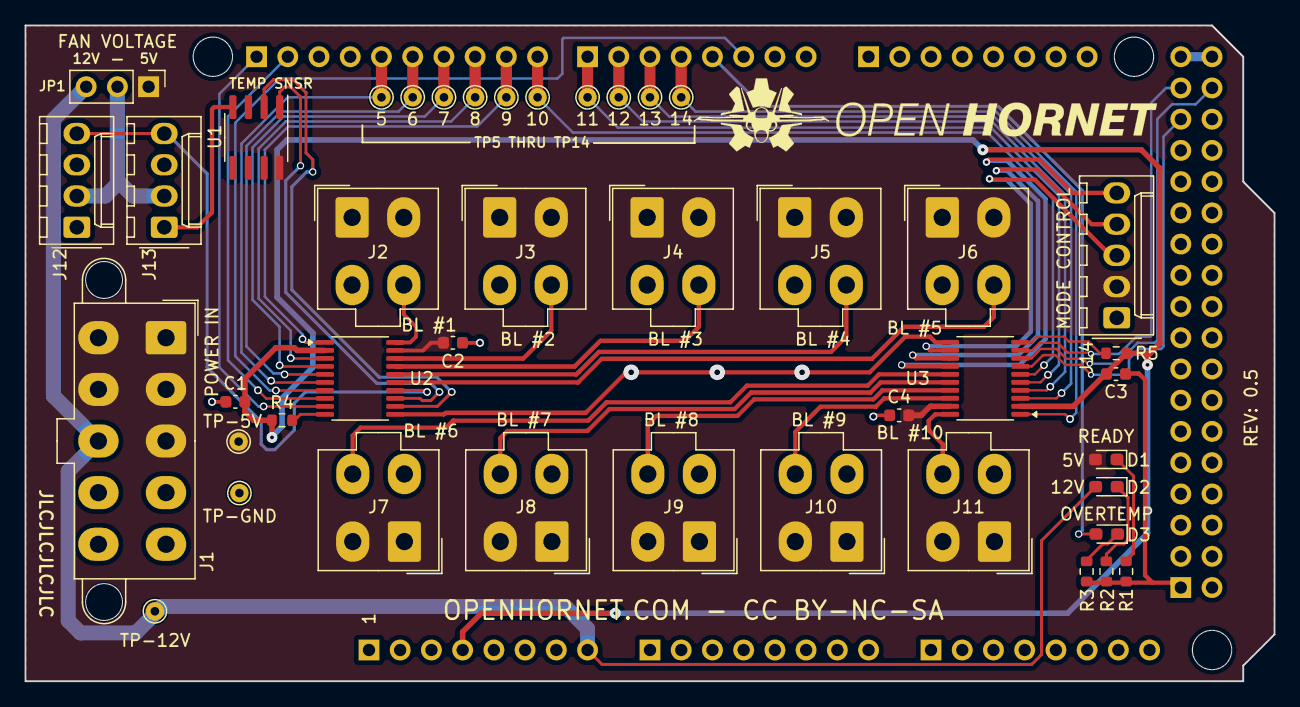
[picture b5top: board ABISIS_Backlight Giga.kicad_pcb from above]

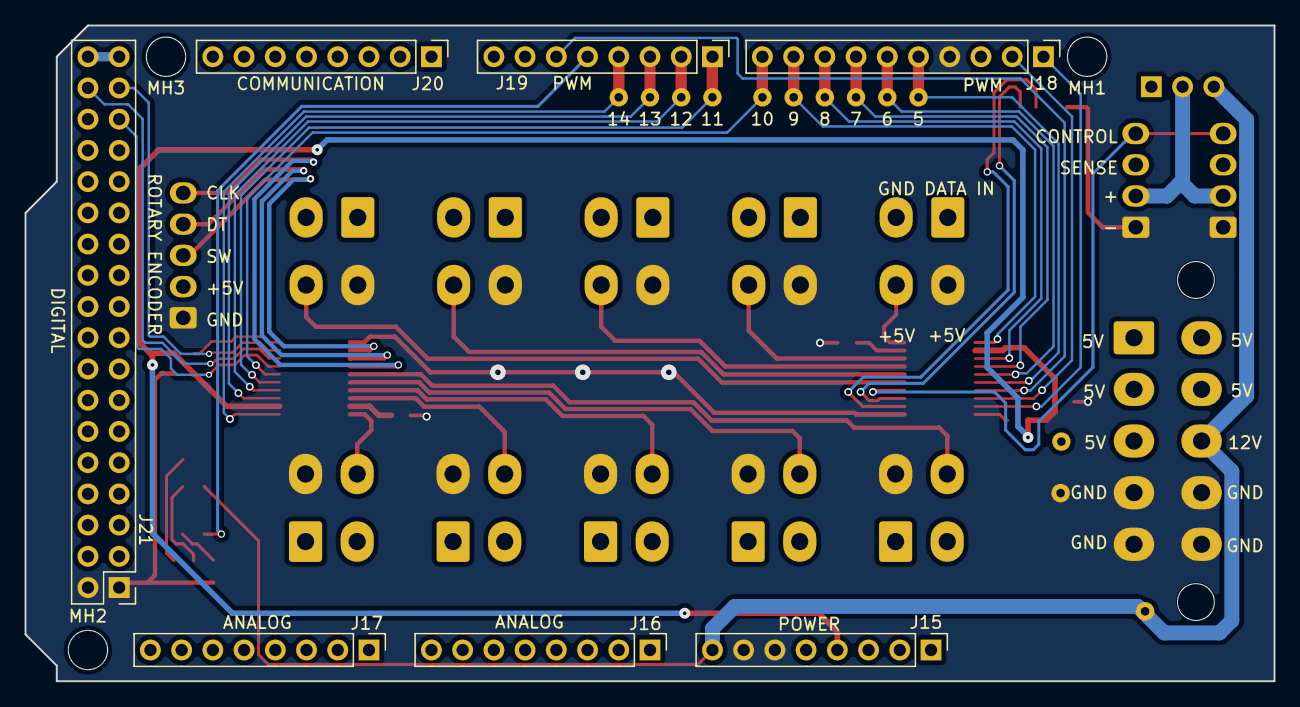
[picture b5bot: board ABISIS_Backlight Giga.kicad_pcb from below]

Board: 2 copper layers, 101.6 x 53.3 mm, 54 parts (10 on the bottom side), 44 nets.
